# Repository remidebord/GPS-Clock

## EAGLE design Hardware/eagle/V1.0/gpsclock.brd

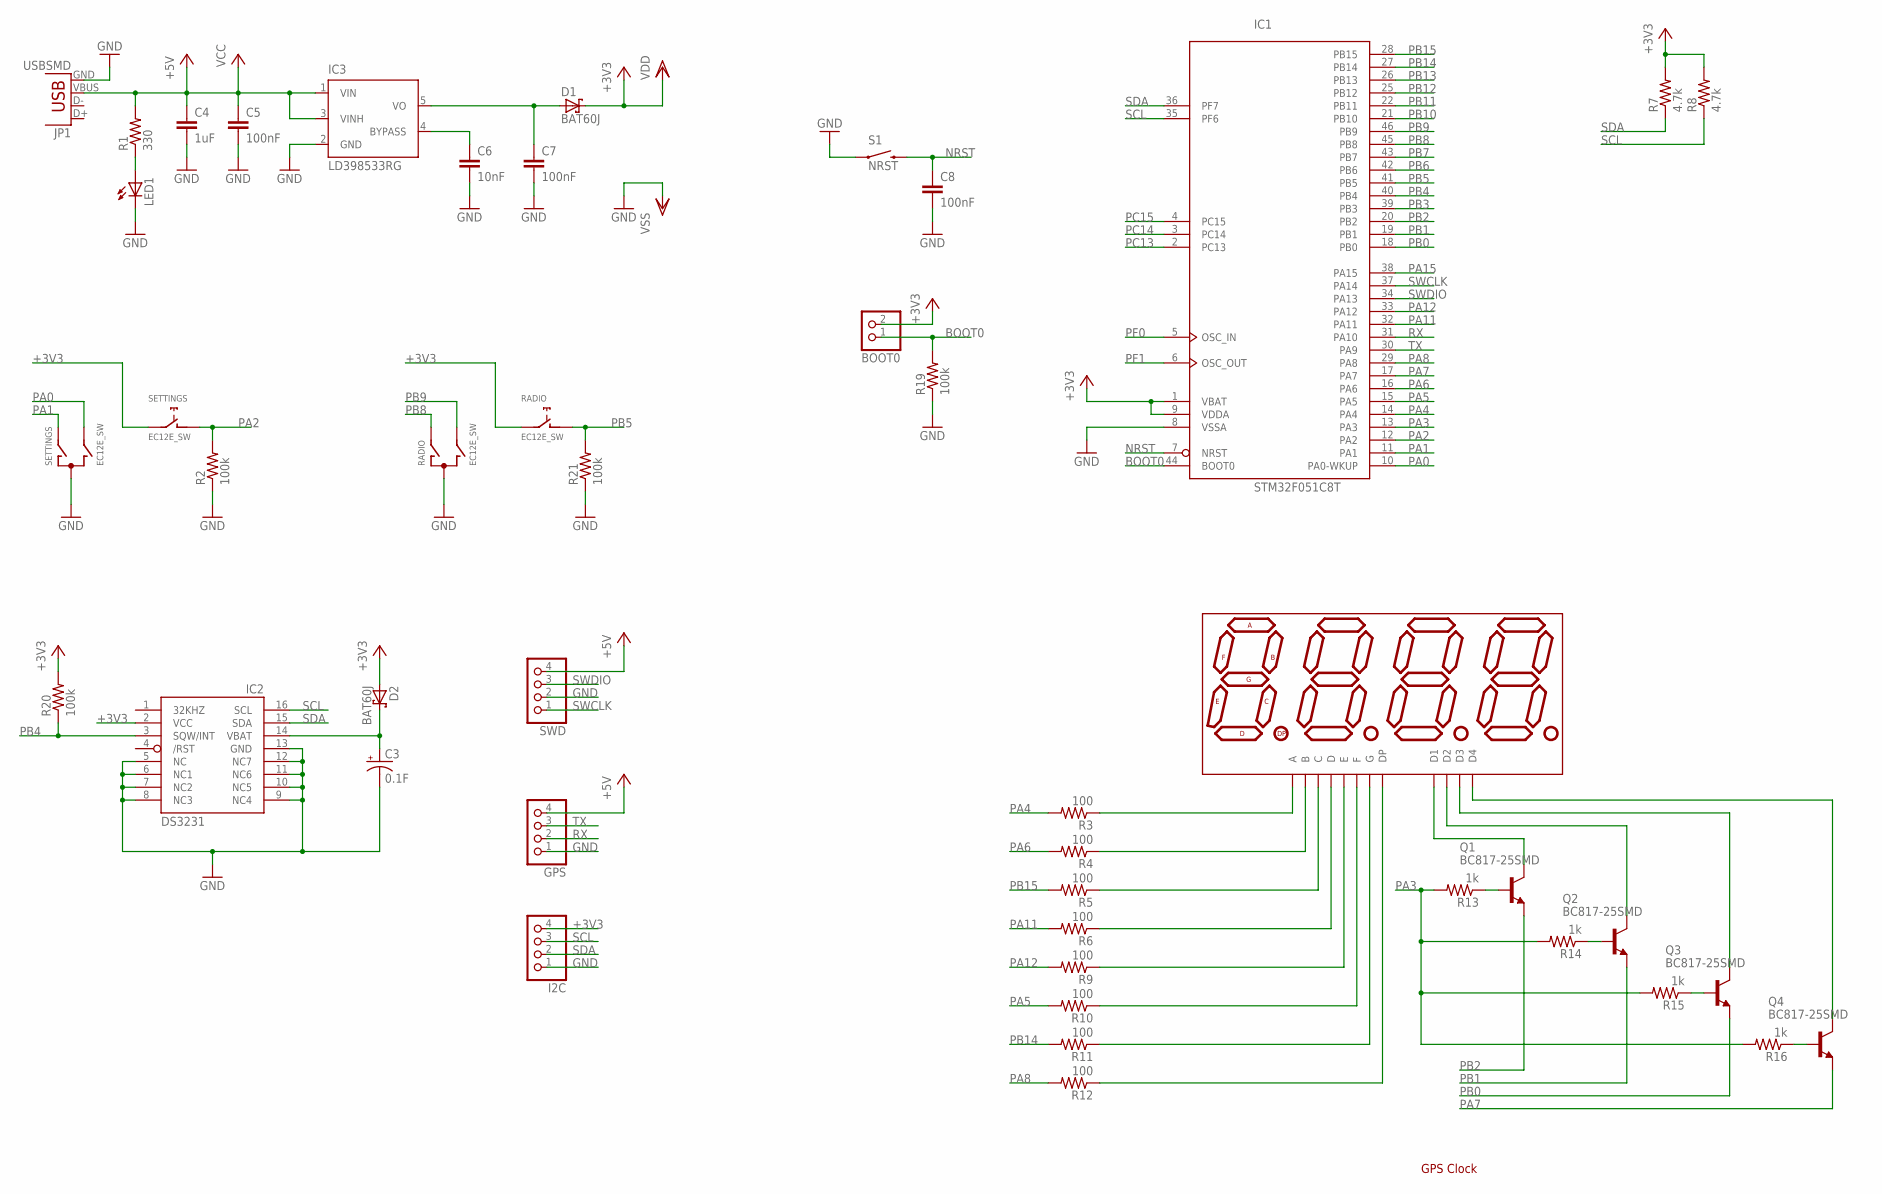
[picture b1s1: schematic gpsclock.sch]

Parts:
7SEG: 7-SEGMENT-4DIGIT-COUNTER; CC56-21SURKWA
BOOT0: PINHD-1X2; 1X02
C3: 0.1F; CPOL-RADIAL-1000UF-25V
C4: 1uF; C0805
C5, C7, C8: 100nF; C1206
C6: 10nF; C0805
D1, D2: BAT60J; SOD323_ST
GPS: PINHD-1X4; 1X04
I2C: PINHD-1X4; 1X04
IC1: STM32F051C8T; LQFP48
IC2: DS3231/SO; SO16W
IC3: LD398533RG; TSOT23-5L
JP1: USBSMD; USB-MINIB
LED1: LEDCHIPLED_1206; CHIPLED_1206
Q1, Q2, Q3, Q4: BC817-25SMD; SOT23-BEC
R1: 330; R1206
R2, R19, R20, R21: 100k; R1206
R3, R4, R5, R6, R9, R10, R11, R12: 100; R1206
R7, R8: 4.7k; R0805
R13, R14, R15, R16: 1k; R1206
RADIO: EC12E_SW; ALPS_EC12E_SW
S1: NRST; TACTILE-SWITCH-SMD
SETTINGS: EC12E_SW; ALPS_EC12E_SW
SWD: PINHD-1X4; 1X04

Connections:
+3V3: BOOT0.2, D1.C, D2.A, I2C.4, IC1.1 (VBAT), IC1.9 (VDDA), IC1.24 (VDD), IC1.48 (VDD), IC2.2 (VCC), R7.2, R8.2, R20.2, RADIO.E (2), SETTINGS.E (2)
+5V: C4.1, C5.1, GPS.4, IC3.1 (VIN), IC3.3 (VINH), JP1.VBUS, R1.2, SWD.4
BOOT0: BOOT0.1, IC1.44 (BOOT0), R19.2
GND: C3.2 (-), C4.2, C5.2, C6.2, C7.2, C8.2, GPS.1, I2C.1, IC1.8 (VSSA), IC1.23 (VSS), IC1.47 (VSS), IC2.5 (NC), IC2.6 (NC1), IC2.7 (NC2), IC2.8 (NC3), IC2.9 (NC4), IC2.10 (NC5), IC2.11 (NC6), IC2.12 (NC7), IC2.13 (GND), IC3.2 (GND), JP1.GND, LED1.C, R2.1, R19.1, R21.1, RADIO.C, S1.1, S1.2 (1), SETTINGS.C, SWD.2
unnamed: 7SEG.10 (F), R10.1
unnamed: 7SEG.9 (D2), Q2.C
unnamed: 7SEG.6 (D4), Q4.C
unnamed: LED1.A, R1.1
unnamed: Q2.B, R14.1
unnamed: 7SEG.11 (A), R3.1
unnamed: 7SEG.7 (B), R4.1
unnamed: C6.1, IC3.4 (BYPASS)
unnamed: C7.1, D1.A, IC3.5 (VO)
unnamed: 7SEG.4 (C), R5.1
unnamed: 7SEG.2 (D), R6.1
unnamed: 7SEG.1 (E), R9.1
unnamed: 7SEG.5 (G), R11.1
unnamed: 7SEG.3 (DP), R12.1
unnamed: Q3.B, R15.1
unnamed: 7SEG.8 (D3), Q3.C
unnamed: C3.1 (+), D2.C, IC2.14 (VBAT)
unnamed: Q1.B, R13.1
unnamed: 7SEG.12 (D1), Q1.C
unnamed: Q4.B, R16.1
NRST: C8.1, IC1.7 (NRST), S1.3 (2), S1.4 (2)
PA0: IC1.10 (PA0-WKUP), SETTINGS.B
PA1: IC1.11 (PA1), SETTINGS.A
PA2: IC1.12 (PA2), R2.2, SETTINGS.D (1)
PA3: IC1.13 (PA3), R13.2, R14.2, R15.2, R16.2
PA4: IC1.14 (PA4), R3.2
PA5: IC1.15 (PA5), R10.2
PA6: IC1.16 (PA6), R4.2
PA7: IC1.17 (PA7), Q4.E
PA8: IC1.29 (PA8), R12.2
PA11: IC1.32 (PA11), R6.2
PA12: IC1.33 (PA12), R9.2
PA15: IC1.38 (PA15)
PB0: IC1.18 (PB0), Q3.E
PB1: IC1.19 (PB1), Q2.E
PB2: IC1.20 (PB2), Q1.E
PB3: IC1.39 (PB3)
PB4: IC1.40 (PB4), IC2.3 (SQW/INT), R20.1
PB5: IC1.41 (PB5), R21.2, RADIO.D (1)
PB6: IC1.42 (PB6)
PB7: IC1.43 (PB7)
PB8: IC1.45 (PB8), RADIO.A
PB9: IC1.46 (PB9), RADIO.B
PB10: IC1.21 (PB10)
PB11: IC1.22 (PB11)
PB12: IC1.25 (PB12)
PB13: IC1.26 (PB13)
PB14: IC1.27 (PB14), R11.2
PB15: IC1.28 (PB15), R5.2
PC13: IC1.2 (PC13)
PC14: IC1.3 (PC14)
PC15: IC1.4 (PC15)
PF0: IC1.5 (OSC_IN)
PF1: IC1.6 (OSC_OUT)
RX: GPS.2, IC1.31 (PA10)
SCL: I2C.3, IC1.35 (PF6), IC2.16 (SCL), R8.1
SDA: I2C.2, IC1.36 (PF7), IC2.15 (SDA), R7.1
SWCLK: IC1.37 (PA14), SWD.1
SWDIO: IC1.34 (PA13), SWD.3
TX: GPS.3, IC1.30 (PA9)

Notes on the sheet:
GPS Clock

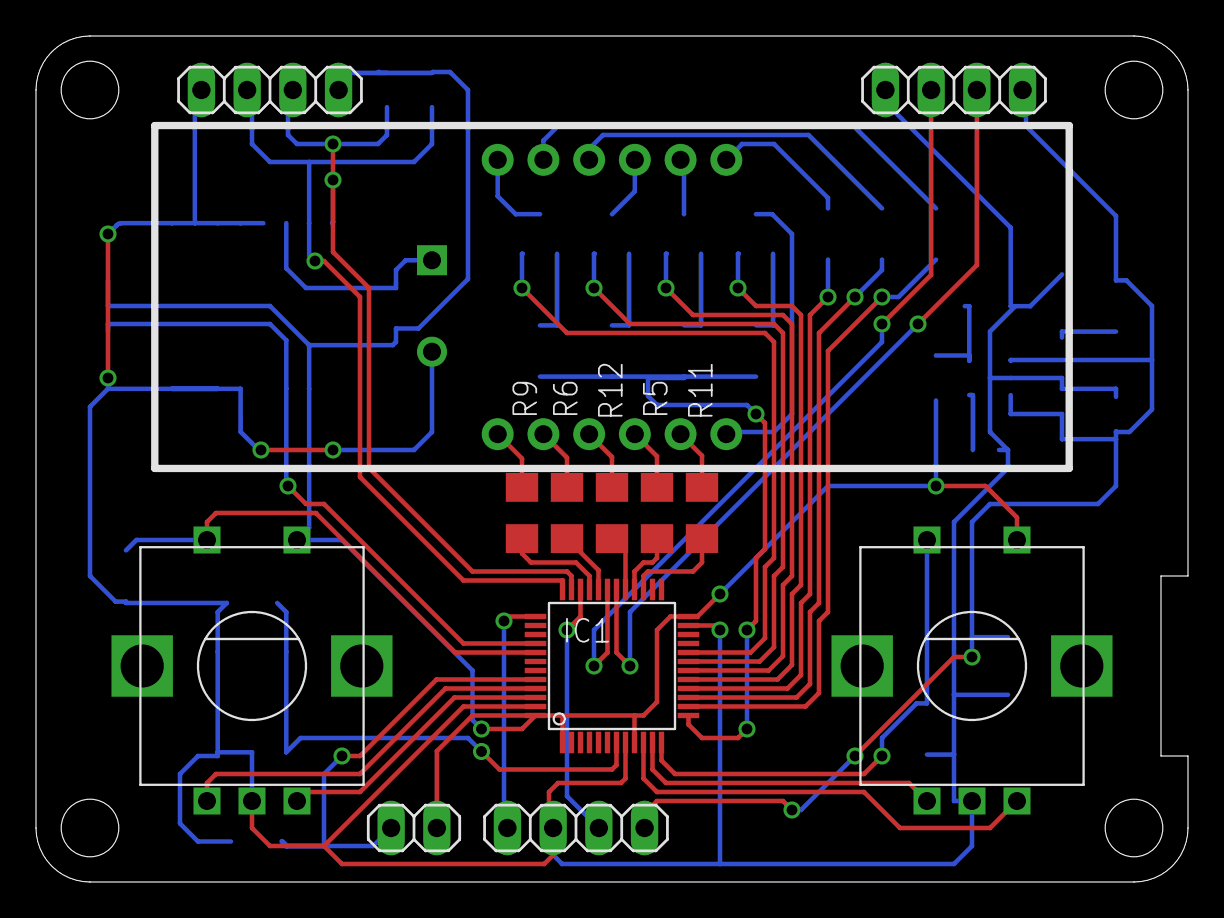
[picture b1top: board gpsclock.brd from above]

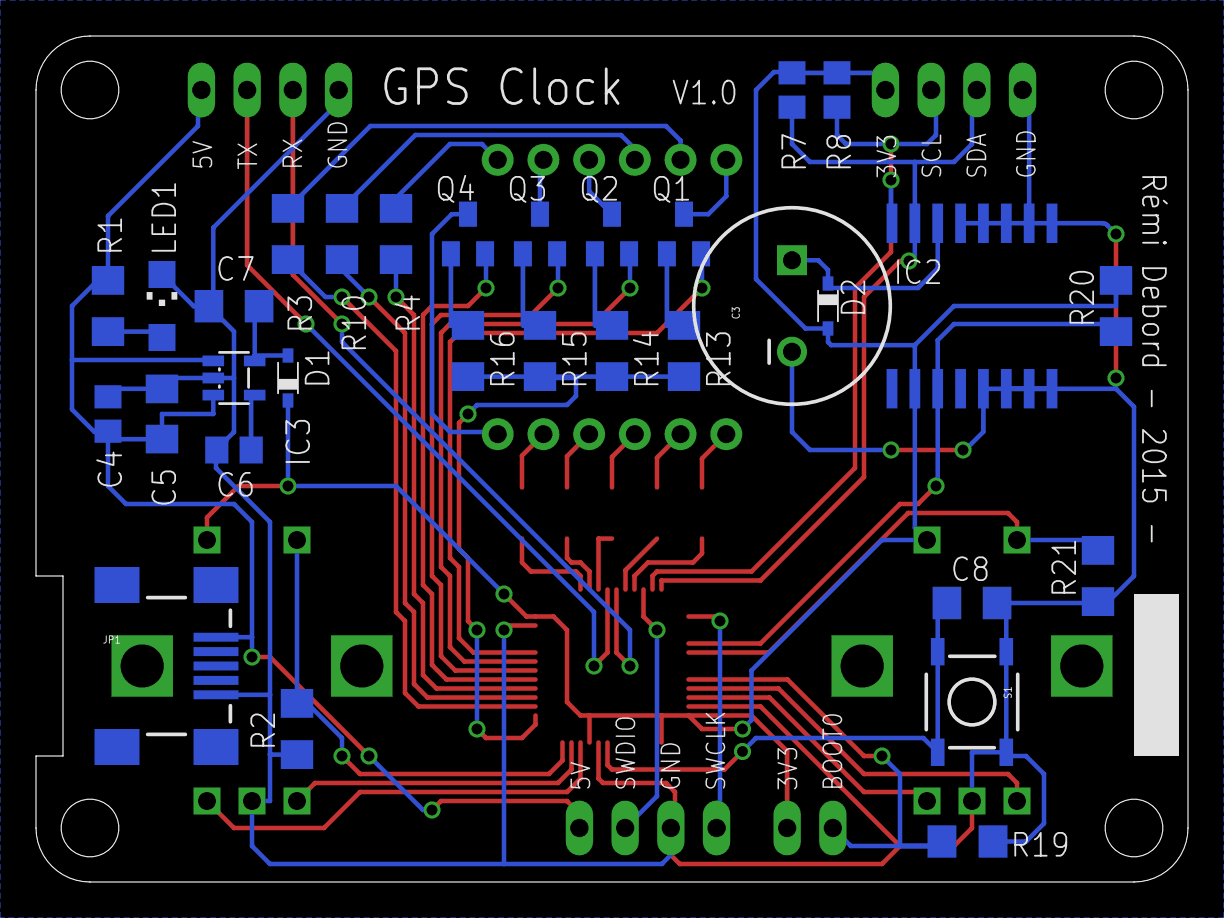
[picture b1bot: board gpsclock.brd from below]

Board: 2 copper layers, 64.0 x 47.0 mm, 44 parts (31 on the bottom side), 51 nets.

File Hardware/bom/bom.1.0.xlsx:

Qty | Price/unit (€) | Price (€) | Stock | Value | Package | Parts | Description | RS | Réf
1 | 0.09 | 0.09 | 50 |  | CHIPLED_1206 | LED1 | LED | 692-1098
1 | 0 | 0 | 100 |  | 1X02 | BOOT0 | PIN HEADER | /
3 | 0 | 0 | 100 |  | 1X04 | GPS, I2C, SWD | PIN HEADER | /
1 | 2.6 | 2.6 | 2 | 0.1F or 0.22F | CPOL-RADIAL-1000UF-25V | C3 | Capacitor Polarized | 867-5463
8 | 0.01 | 0.08 | 42 | 100 or 200 | R1206 | R3, R4, R5, R6, R9, R10, R11, R12 | RESISTOR, American symbol | 740-9079 | CR1206-FX-1000ELF
4 | 0.02 | 0.08 | 50 | 100k | R1206 | R2, R19, R20, R21 | RESISTOR, American symbol | 740-9114 | CR1206-JW-104GLF
3 | 0.08 | 0.24 | 49 | 100nF | C1206 | C5, C7, C8 | CAPACITOR, European symbol | 464-6852 | 12065C104JAT1A
1 | 0.03 | 0.03 | 24 | 10nF | C0805 | C6 | CAPACITOR, European symbol | 264-4371 | C0805C103K5RACTU
4 | 0.02 | 0.08 | 46 | 1k | R1206 | R13, R14, R15, R16 | RESISTOR, American symbol | 740-9088 | CR1206-FX-1001ELF
1 | 0.03 | 0.03 | 48 | 1uF | C0805 | C4 | CAPACITOR, European symbol | 691-1167 | C0805C105K3RACTU
1 | 0.13 | 0.13 | 89 | 330 | R1206 | R1 | RESISTOR, American symbol | 8121871 | CRCW1206330RFKEAHP
2 | 0.01 | 0.02 | 49 | 4.7k | R0805 | R7, R8 | RESISTOR, American symbol | 223-0528 | CRG0805F4K7
1 | 3.64 | 3.64 | 1 | 7-SEGMENT-4DIGIT-COUNTER | CC56-21SURKWA | 7SEG |  | 8722014 | CC56-21SURKWA
2 | 0.31 | 0.62 | 49 | BAT20J | SOD323_ST | D1, D2 | Schottky barrier diode | 714-6844 | BAT20JFILM
4 | 0.12 | 0.48 | 24 | BC817-25SMD | SOT23-BEC | Q1, Q2, Q3, Q4 | NPN Transistor | 690-0076 | BC817-25LT3G
1 | 10.24 | 10.24 | 3 | DS3231/SO | SO16W | IC2 |  | 732-7582 | DS3231SN#
2 | 2.16 | 4.32 | 6 | EC12E_SW | PEC11R-4215F-S0024 | RADIO, SETTINGS | Bourns rotary Encoder PEC11R series with switch | 737-7748 | PEC11R-4215F-S0024
1 | 0.62 | 0.62 | 4 | LD398533RG | TSOT23-5L | IC3 | Ultra low drop and low noise BiCMOS voltage regulators | 686-8802 | LD3985M33R
1 | 0.38 | 0.38 | 9 | NRST | TACTILE-SWITCH-SMD | S1 | Various NO switches- pushbuttons, reed, etc | 758-2060 | SKQGAFE010
1 | 1.83 | 1.83 | 4 | STM32F051C8T | LQFP48 | IC1 | ARM 32-bit Cortex™-M0 CPU | 761-8658 | STM32F051C8T6
1 | 1.17 | 1.17 | 4 | USBSMD | USB-MINIB | JP1 | USB Connectors | 670-2654 | 67503-1230
 | Total | 26.68 | €
 | PCB | 7.76 | € | > OSH (23,30€ pour 3)
 | Plexi | 2.48 | € | > Damengo (9,95€ pour 4)
 | Vis | 3 | € | > http://www.futurlec.com/Hardware.shtml (2€ pour 12 entretoises + vis) + Brico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
 | GPS | 17 | € | > TxHang Electronic (ebay) => version NEO M8N
 | Total | 56.919999999999995 | €

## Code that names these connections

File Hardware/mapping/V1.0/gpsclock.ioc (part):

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Mcu.Name=STM32F051C8Tx
Mcu.Package=LQFP48
Mcu.UserName=STM32F051C8Tx
PA0.Signal=GPXTI0
PA1.Signal=GPXTI1
PA10.Mode=Asynchronous
PA10.Signal=USART1_RX
PA11.Signal=GPIO_Output
PA12.Signal=GPIO_Output
PA13.Mode=Serial-WireDebug
PA13.Signal=SYS_SWDIO
PA14.Mode=Serial-WireDebug
PA14.Signal=SYS_SWCLK
PA2.Signal=GPIO_Input
PA3.Signal=S_TIM15_CH2
PA4.Signal=GPIO_Output
PA5.Signal=GPIO_Output
PA6.Signal=GPIO_Output
PA7.Signal=GPIO_Output
PA8.Signal=GPIO_Output
PA9.Mode=Asynchronous
PA9.Signal=USART1_TX
PB0.Signal=GPIO_Output
PB1.Signal=GPIO_Output
PB14.Signal=GPIO_Output
PB15.Signal=GPIO_Output
PB2.Signal=GPIO_Output
PB4.Signal=GPXTI4
PB5.Signal=GPIO_Input
PB8.Signal=GPXTI8
PB9.Signal=GPXTI9
PF6.Mode=I2C
PF6.Signal=I2C2_SCL
PF7.Mode=I2C
PF7.Signal=I2C2_SDA

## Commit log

2016-12-22 :boom::camel: Added .gitattributes & .gitignore files
2016-12-22 GPS Clock V1.0
    First commit !

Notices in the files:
parts and their libraries:
SparkFun-Passives: Licensing: Creative Commons ShareAlike 4.0 International - https://creativecommons.org/licenses/by-sa/4.0
